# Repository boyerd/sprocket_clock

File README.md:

Sprocket Clock

==============

A gear clock build from a driven spur gear and a large inner gear that rides on it.  The spur gear indicates minutes and the large inner gear indicates the hour.

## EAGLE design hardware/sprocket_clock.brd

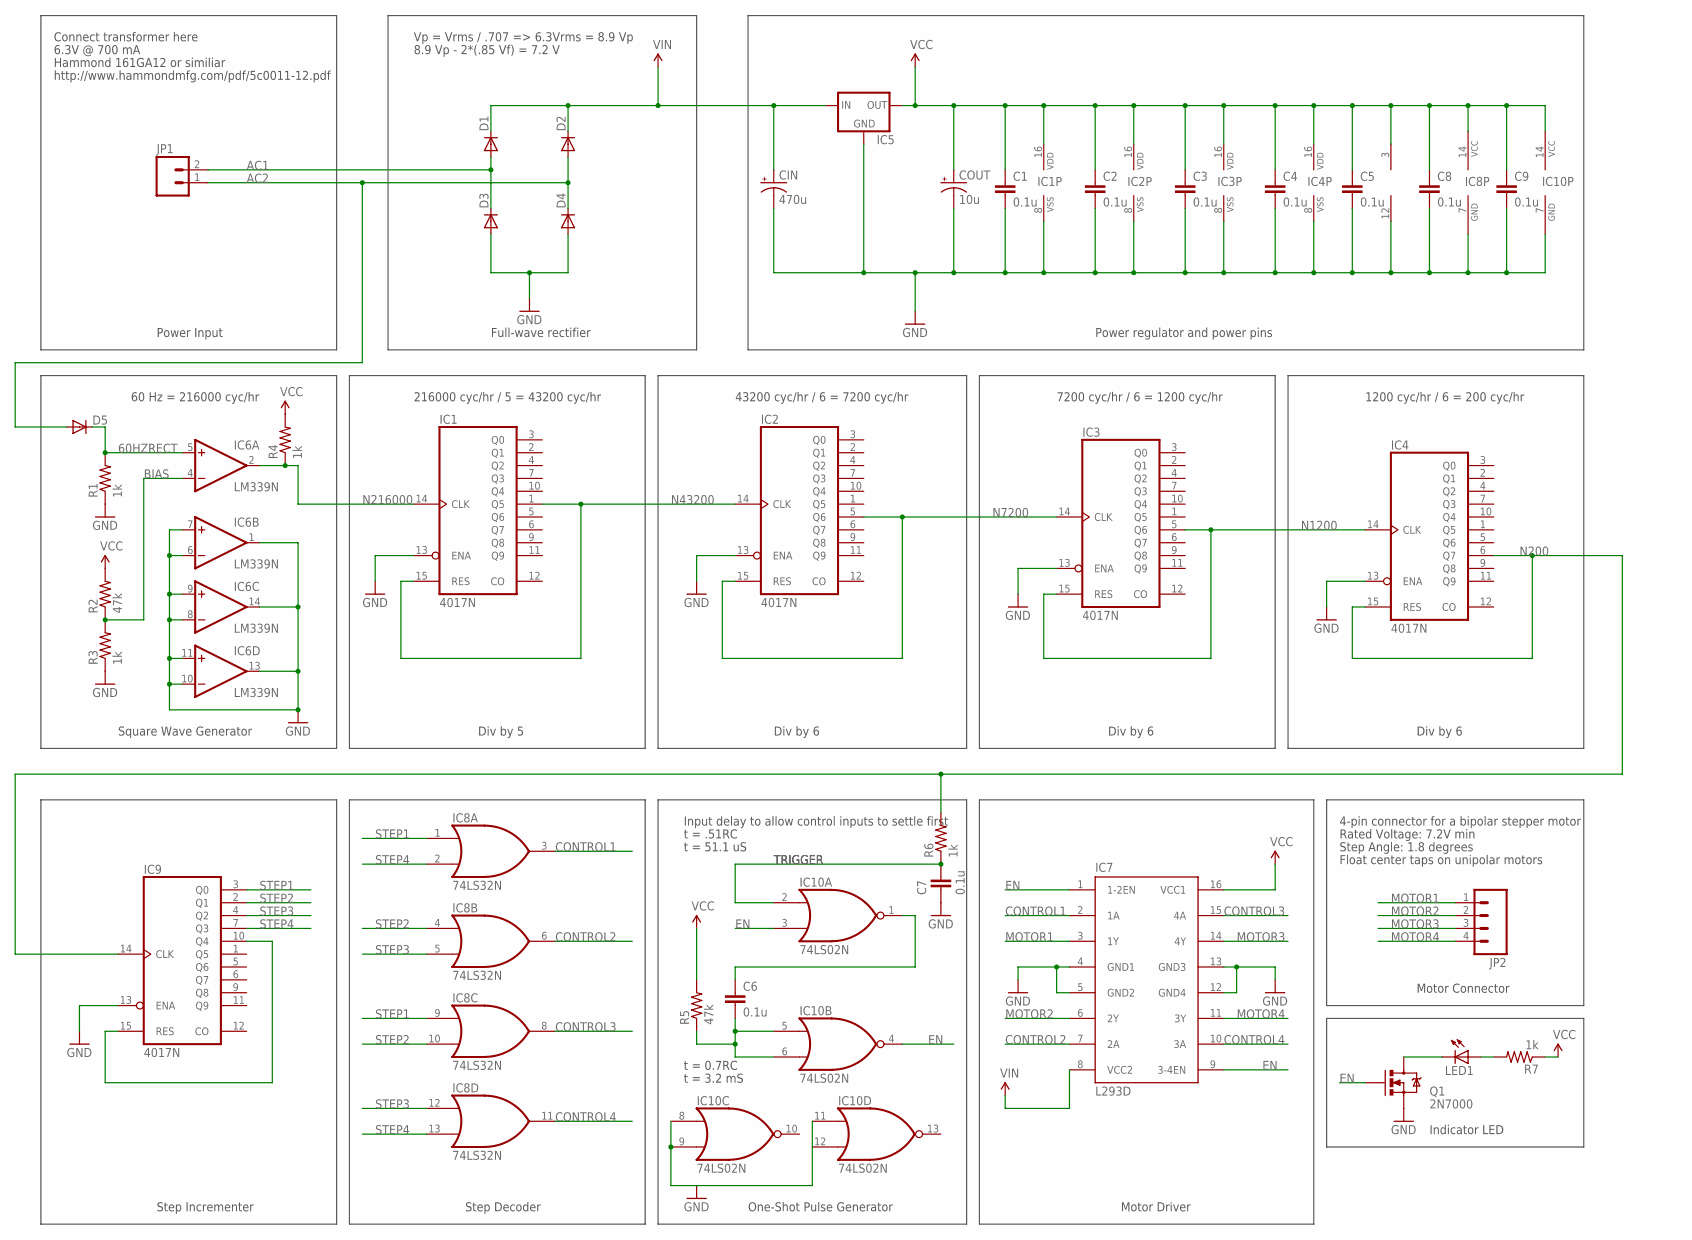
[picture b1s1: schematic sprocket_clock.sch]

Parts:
C1, C2, C3, C4, C5, C6, C7, C8, C9: 0.1u; CAP-PTH-5MM
CIN: 470u; CPOL-RADIAL-1000UF-63V
COUT: 10u; CPOL-RADIAL-10UF-25V
D1, D2, D3, D4, D5: DIODEPTH; DIODE-1N4001
IC1, IC2, IC3, IC4, IC9: 4017N; DIL16
IC5: V_REG_78XXTO-92; TO-92
IC6: LM339N; DIL14
IC7: L293D; DIL16
IC8: 74LS32N; DIL14
IC10: 74LS02N; DIL14
JP1: M023.5MM-NO_SILK; SCREWTERMINAL-3.5MM-2-NS
JP2: M04SCREW; SCREWTERMINAL-3.5MM-4
LED1: LED5MM
Q1: 2N7000; TO-92
R1, R3, R4, R6, R7: 1k; AXIAL-0.4
R2, R5: 47k; AXIAL-0.4

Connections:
60HZRECT: D5.C, IC6.5 (+IN), R1.P$2 (2)
AC1: D1.A, D3.C, JP1.2
AC2: D2.A, D4.C, D5.A, JP1.1
BIAS: IC6.4 (-IN), R2.P$1 (1), R3.P$2 (2)
CONTROL1: IC7.2 (1A), IC8.3 (O)
CONTROL2: IC7.7 (2A), IC8.6 (O)
CONTROL3: IC7.15 (4A), IC8.8 (O)
CONTROL4: IC7.10 (3A), IC8.11 (O)
EN: IC7.1 (1-2EN), IC7.9 (3-4EN), IC10.3 (I1), IC10.4 (O), Q1.2 (G)
GND: C1.2, C2.2, C3.2, C4.2, C5.2, C7.2, C8.2, C9.2, CIN.2 (-), COUT.2 (-), D3.A, D4.A, IC1.8 (VSS), IC1.13 (ENA), IC2.8 (VSS), IC3.8 (VSS), IC4.8 (VSS), IC5.1 (GND), IC6.1 (OUT), IC6.6 (-IN), IC6.7 (+IN), IC6.8 (-IN), IC6.9 (+IN), IC6.10 (-IN), IC6.11 (+IN), IC6.12 (GND), IC6.13 (OUT), IC6.14 (OUT), IC7.4 (GND1), IC7.5 (GND2), IC7.12 (GND4), IC7.13 (GND3), IC8.7 (GND), IC10.7 (GND), Q1.1 (S), R1.P$1 (1), R3.P$1 (1)
MOTOR1: IC7.3 (1Y), JP2.1
MOTOR2: IC7.6 (2Y), JP2.2
MOTOR3: IC7.14 (4Y), JP2.3
MOTOR4: IC7.11 (3Y), JP2.4
N200: IC4.6 (Q7), IC4.15 (RES), IC9.14 (CLK), R6.P$2 (2)
N1200: IC3.5 (Q6), IC3.15 (RES), IC4.14 (CLK)
N7200: IC2.5 (Q6), IC2.15 (RES), IC3.14 (CLK)
N43200: IC1.1 (Q5), IC1.15 (RES), IC2.14 (CLK)
N216000: IC1.14 (CLK), IC6.2 (OUT), R4.P$1 (1)
unnamed: LED1.A, R7.P$2 (2)
unnamed: IC9.10 (Q4), IC9.15 (RES)
unnamed: C6.1, IC10.1 (O)
unnamed: C6.2, IC10.5 (I0), IC10.6 (I1), R5.P$1 (1)
unnamed: LED1.K (C), Q1.3 (D)
unnamed: IC10.8 (I0), IC10.9 (I1), IC10.11 (I0)
STEP1: IC8.1 (I0), IC8.9 (I0), IC9.3 (Q0)
STEP2: IC8.4 (I0), IC8.10 (I1), IC9.2 (Q1)
STEP3: IC8.5 (I1), IC8.12 (I0), IC9.4 (Q2)
STEP4: IC8.2 (I1), IC8.13 (I1), IC9.7 (Q3)
TRIGGER: C7.1, IC10.2 (I0), R6.P$1 (1)
VCC: C1.1, C2.1, C3.1, C4.1, C5.1, C8.1, COUT.1 (+), IC1.16 (VDD), IC2.16 (VDD), IC3.16 (VDD), IC4.16 (VDD), IC5.3 (OUT), IC6.3 (V+), IC7.16 (VCC1), IC8.14 (VCC), IC10.14 (VCC), R2.P$2 (2), R4.P$2 (2), R5.P$2 (2), R7.P$1 (1)
VDD: IC9.16 (VDD)
VIN: CIN.1 (+), D1.C, D2.C, IC5.2 (IN), IC7.8 (VCC2)
VSS: IC9.8 (VSS)

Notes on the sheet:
Div by 5
Div by 6
http://www.hammondmfg.com/pdf/5c0011-12.pdf
Connect transformer here
6.3V @ 700 mA
Hammond 161GA12 or similiar
Vp = Vrms / .707 => 6.3Vrms = 8.9 Vp
8.9 Vp - 2*(.85 Vf) = 7.2 V
Power Input
Full-wave rectifier
Power regulator and power pins
Square Wave Generator
60 Hz = 216000 cyc/hr
216000 cyc/hr / 5 = 43200 cyc/hr
43200 cyc/hr / 6 = 7200 cyc/hr
7200 cyc/hr / 6 = 1200 cyc/hr
1200 cyc/hr / 6 = 200 cyc/hr
Step Incrementer
Step Decoder
One-Shot Pulse Generator
Motor Driver
Motor Connector
4-pin connector for a bipolar stepper motor
Step Angle: 1.8 degrees
Float center taps on unipolar motors
Rated Voltage: 7.2V min
t = 0.7RC
t = .51RC
t = 51.1 uS
Input delay to allow control inputs to settle first
Indicator LED
t = 3.2 mS

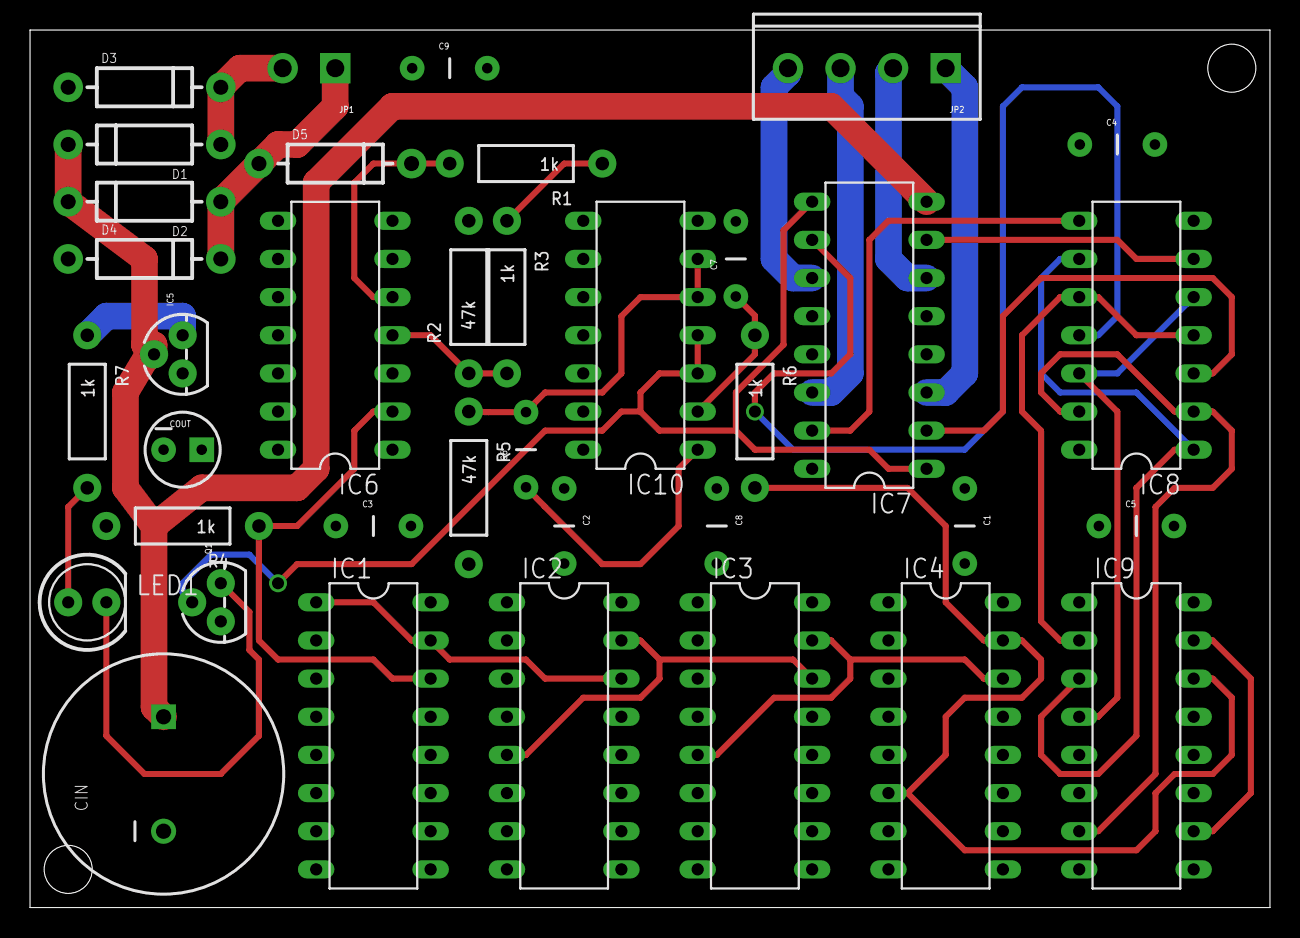
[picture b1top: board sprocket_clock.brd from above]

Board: 2 copper layers, 82.5 x 58.4 mm, 37 parts (0 on the bottom side), 32 nets.

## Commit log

2014-10-12 Adds the initial version of the board and schematic file.

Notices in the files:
parts and their libraries:
SparkFun-Capacitors: Licensing: CC v3.0 Share-Alike You are welcome to use this library for commercial purposes.
